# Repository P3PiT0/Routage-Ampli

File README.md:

# Routage-Ampli
Partie routage du BE d'électronique(3IMACS) 

**Schéma OK

**Relais (Symb[Relay] + Foodprint[Mes_Empreintes.pretty]) OK

**Annotation des composants OK

**ERC (Problème avec GND et +/-12V et Borne TN JackMono)

**Attribution des Empreintes OK 

**Changement de la librairie (TR_LibAmpli_3imacs_2021) OK

**NETLIST OK

**DRC OK 

**Délimitation PCB + Placement OK 

**Routage, piste de puissance et plan de masse en attente de GO

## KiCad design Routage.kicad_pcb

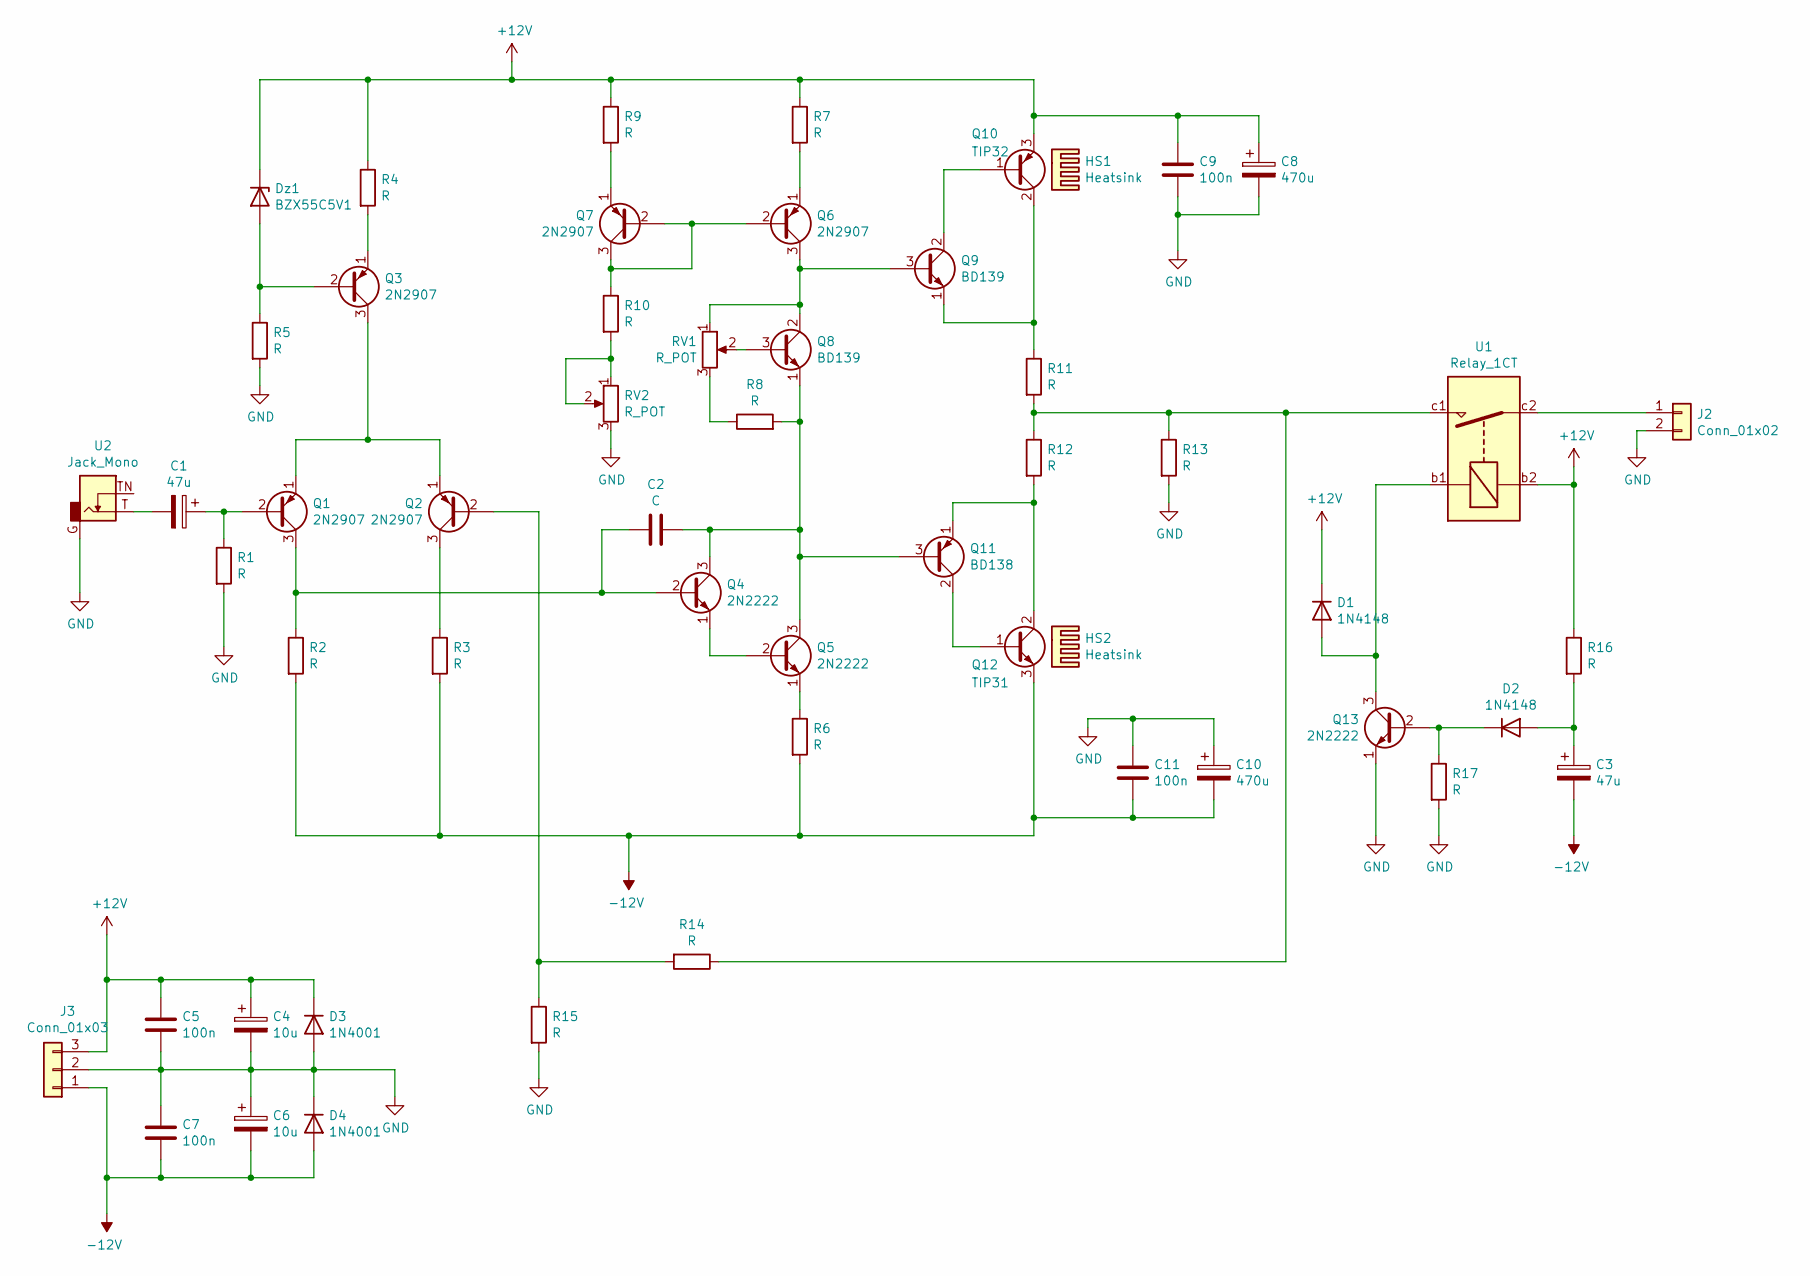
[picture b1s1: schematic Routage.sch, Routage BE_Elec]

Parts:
C1, C3: 47u; CP_Radial_D8.0mm_P5.00mm
C2: C; C_Rect_L7.2mm_W3.5mm_P5.00mm_FKS2_FKP2_MKS2_MKP2
C4, C6: 10u; CP_Radial_D8.0mm_P5.00mm
C5, C7, C9, C11: 100n; C_Rect_L7.2mm_W3.5mm_P5.00mm_FKS2_FKP2_MKS2_MKP2
C8, C10: 470u; CP_Radial_D12.5mm_P5.00mm
D1, D2: 1N4148; D_DO-35_SOD27_P10.16mm_Horizontal
D3, D4: 1N4001; D_DO-41_SOD81_P10.16mm_Horizontal
Dz1: BZX55C5V1; D_DO-35_SOD27_P10.16mm_Horizontal
HS1, HS2: Heatsink; Heatsink_Fischer_SK104-STC-STIC_35x13mm_2xDrill2.5mm
J2: Conn_01x02; PhoenixContact_MSTBVA_2,5_2-G-5,08_1x02_P5.08mm_Vertical
J3: Conn_01x03; PhoenixContact_MSTBVA_2,5_3-G-5,08_1x03_P5.08mm_Vertical
Q1, Q2, Q3, Q6, Q7: 2N2907; TO-18-3
Q4, Q5, Q13: 2N2222; TO-18-3
Q8, Q9: BD139; TO-126-3_Vertical
Q10: TIP32; TO-220-3_Vertical
Q11: BD138; TO-126-3_Vertical
Q12: TIP31; TO-220-3_Vertical
R1, R2, R3, R4, R5, R6, R7, R8, R9, R10, R13, R14, R15, R16, R17: R; R_Axial_DIN0207_L6.3mm_D2.5mm_P10.16mm_Horizontal
R11, R12: R; R_Axial_DIN0516_L15.5mm_D5.0mm_P20.32mm_Horizontal
RV1, RV2: R_POT; Potentiometer_Bourns_3296W_Vertical
U1: Relay_1CT; Relais_OJ-SS-112LMH2,005
U2: Jack_Mono; Jack_35RAPC2AV

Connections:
+12V: C4.1, C5.1, C8.1, C9.1, D1.1 (K), D3.1 (K), Dz1.1 (K), J3.3, Q10.3 (E), R4.1, R7.1, R9.1, R16.1, U1.b2
-12V: C3.2, C6.2, C7.2, C10.2, C11.2, D4.2 (A), J3.1, Q12.3 (E), R2.2, R3.2, R6.2
GND: C4.2, C5.2, C6.1, C7.1, C8.2, C9.2, C10.1, C11.1, D3.2 (A), D4.1 (K), J2.2, J3.2, Q13.1 (E), R1.2, R5.2, R13.2, R15.2, R17.2, RV2.3, U2.G
unnamed: C1.1, Q1.2 (B), R1.1
unnamed: C1.2, U2.T
unnamed: C2.1, Q4.3 (C), Q5.3 (C), Q8.1 (E), Q11.3 (B), R8.2
unnamed: C2.2, Q1.3 (C), Q4.2 (B), R2.1
unnamed: C3.1, D2.2 (A), R16.2
unnamed: D1.2 (A), Q13.3 (C), U1.b1
unnamed: D2.1 (K), Q13.2 (B), R17.1
unnamed: Dz1.2 (A), Q3.2 (B), R5.1
unnamed: J2.1, U1.c2
unnamed: Q1.1 (E), Q2.1 (E), Q3.3 (C)
unnamed: Q2.2 (B), R14.2, R15.1
unnamed: Q2.3 (C), R3.1
unnamed: Q3.1 (E), R4.2
unnamed: Q4.1 (E), Q5.2 (B)
unnamed: Q5.1 (E), R6.1
unnamed: Q6.1 (E), R7.2
unnamed: Q6.2 (B), Q7.2 (B), Q7.3 (C), R10.1
unnamed: Q6.3 (C), Q8.2 (C), Q9.3 (B), RV1.1
unnamed: Q7.1 (E), R9.2
unnamed: Q8.3 (B), RV1.2
unnamed: Q9.2 (C), Q10.1 (B)
unnamed: Q9.1 (E), Q10.2 (C), R11.1
unnamed: Q11.1 (E), Q12.2 (C), R12.2
unnamed: Q11.2 (C), Q12.1 (B)
unnamed: R8.1, RV1.3
unnamed: R10.2, RV2.1, RV2.2
unnamed: R11.2, R12.1, R13.1, R14.1, U1.c1

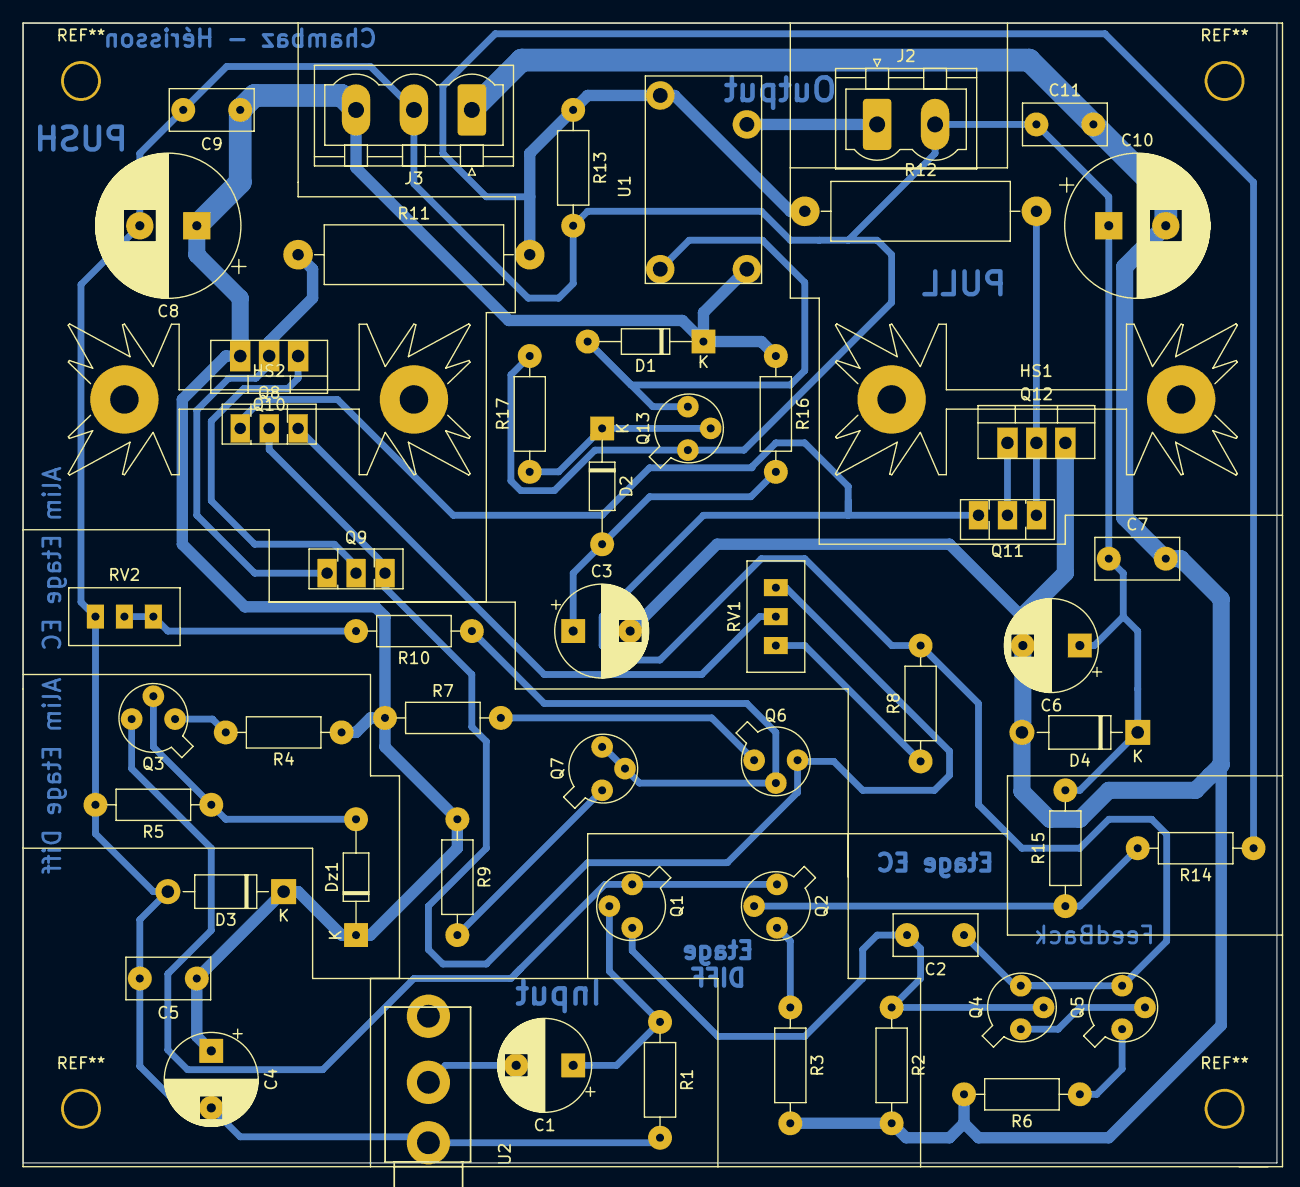
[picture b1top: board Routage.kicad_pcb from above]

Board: 2 copper layers, 110.0 x 100.0 mm, 54 parts (0 on the bottom side), 30 nets.

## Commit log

2021-03-28 Schéma & Relais (Symb+Foodprint)
2021-03-28 ERC (pb GND, 12V et TNjack) + attribution des empreintres (pb C10u, incertitude R11 & R12 => 2W , Rpot?)
2021-04-04 Version 1 du placement avec changement de librairie fait
2021-04-08 Version 2 du placement + DRC
2021-04-08 Placement_V2 après validation et correction des derniers détails
2021-04-11 V1 du routage + Changement placement + rajout diode + Pb masse
2021-04-11 V2 Routage après avoir refait le placement
2021-04-13 Version finale avec les derniers défauts corrigés
2021-04-15 Version finale, validée
